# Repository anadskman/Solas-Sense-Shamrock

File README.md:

# Solas-Sense-Shamrock

A LED Lamp shaped like a shamrock that changes led color based off the room brightness.
I Named it Solas Sense so I can make different designs and Keep it simply orginized.

### My Experience
This was an easier project than most but its still fun and unquie. 
I struggled on the Designing as its an odd shape compared to just squares and a circle or two.

### Parts
- 1x Esp32-C3 SuperMini
- 3x RGB Leds Anode
- 1x Light Dependent Resistors
- 9x 220Omh Resistors
- 1x 10kOmh Resistor

- Top-Case.stl
- Bottom-Case.stl
- SolasSense-Code.ino

## BOM

| Item                    | Description         | Qty | Price (€) | URL                                                                 | Total (€) |
|-------------------------|---------------------|-----|-----------|----------------------------------------------------------------------|----------------|
| 0603 220Ω Chip          | 220Ω Resistor       | 9   | 2.07      | https://www.aliexpress.com/item/1005002783191633.html               | 2.07           |
| RGB LEDs (Anode)        | RGB LEDs (Anode)    | 3   | —         | — Pre owned                                                         | —              |
| Light Dependent Resistor| LDR                 | 1   | —         | — Pre owned                                                         | —              |
| 1005 10kΩ Chip          | 10kΩ Resistor       | 1   | 1.47      | https://www.aliexpress.com/item/1005003297094344.html               | 1.47           |
| ESP32-C3 SuperMini      | Dev Board           | 1   | 2.83      | https://www.aliexpress.com/item/1005009495310442.html               | 2.83           |
|                         |                     |     |           |                                                                     | Shipping: €1.99 | 
|                         |                      |    |            |                                                                    |Total: €8.36     |

 Schematic            |  PCB         |   Case
:-------------------------:|:-------------------------:|:-------------------------:|
 |  |

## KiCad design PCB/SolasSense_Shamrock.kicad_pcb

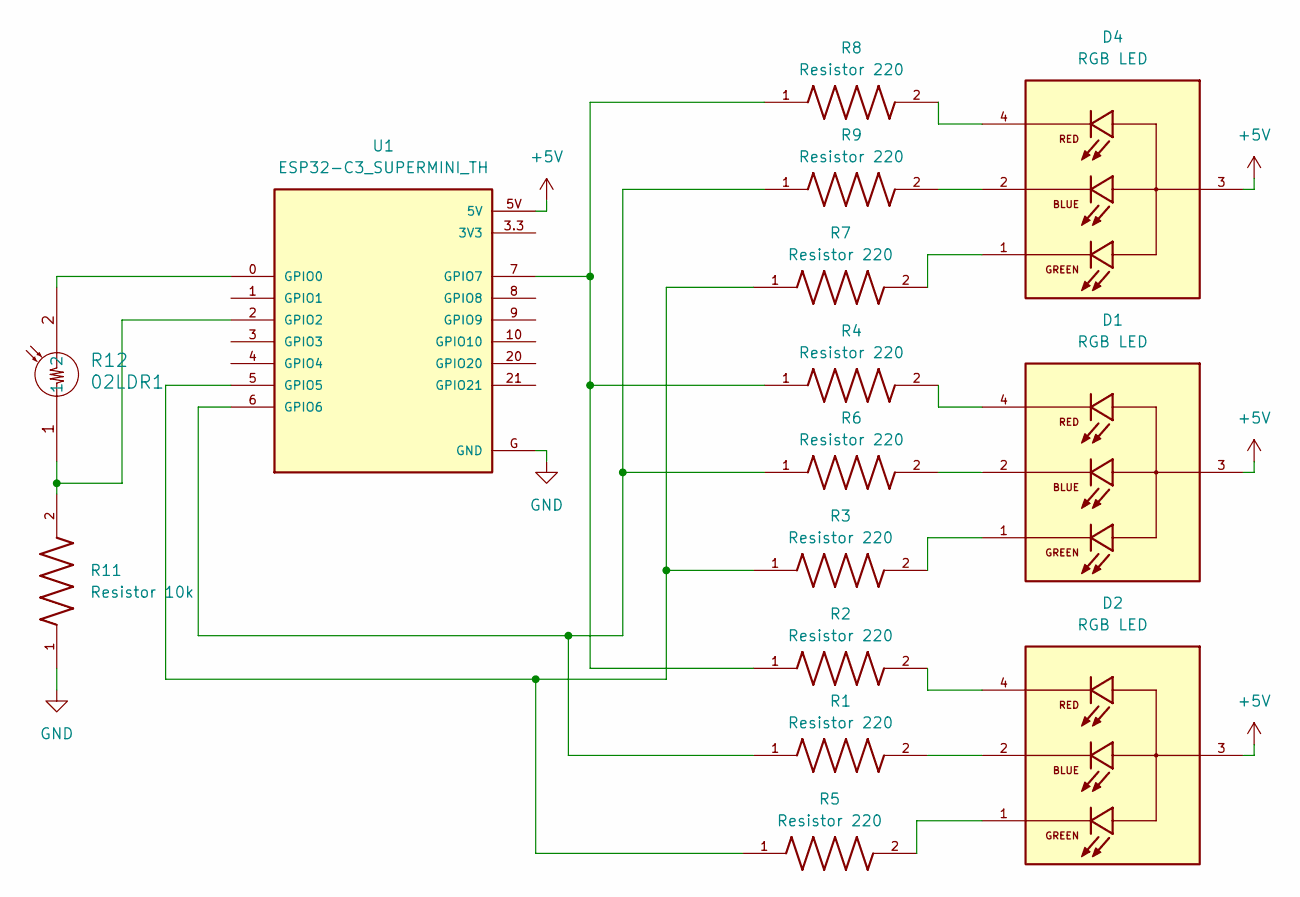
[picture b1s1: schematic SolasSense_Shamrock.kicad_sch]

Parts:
D1, D2, D4: RGB LED; LED_QBL8RGB60D0-2897; PARTREV 1.0
R1, R2, R3, R4, R5, R6, R7, R8, R9: Resistor 220; R_Axial_DIN0204_L3.6mm_D1.6mm_P5.08mm_Vertical
R11: Resistor 10k; R_Axial_DIN0204_L3.6mm_D1.6mm_P5.08mm_Vertical
R12: 02LDR1; LDR1_NTE
U1: ESP32-C3_SUPERMINI_TH; MODULE_ESP32-C3_SUPERMINI_TH

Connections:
+5V: D1.3, D2.3, D4.3, U1.5V
GND: R11.1, U1.G (GND)
unnamed: D1.1, R3.2
unnamed: D1.2, R6.2
unnamed: D1.4, R4.2
unnamed: D2.1, R5.2
unnamed: D2.2, R1.2
unnamed: D2.4, R2.2
unnamed: D4.1, R7.2
unnamed: D4.2, R9.2
unnamed: D4.4, R8.2
unnamed: R12.2, U1.0 (GPIO0)
unnamed: R11.2, R12.1, U1.2 (GPIO2)
unnamed: R3.1, R5.1, R7.1, U1.5 (GPIO5)
unnamed: R1.1, R6.1, R9.1, U1.6 (GPIO6)
unnamed: R2.1, R4.1, R8.1, U1.7 (GPIO7)

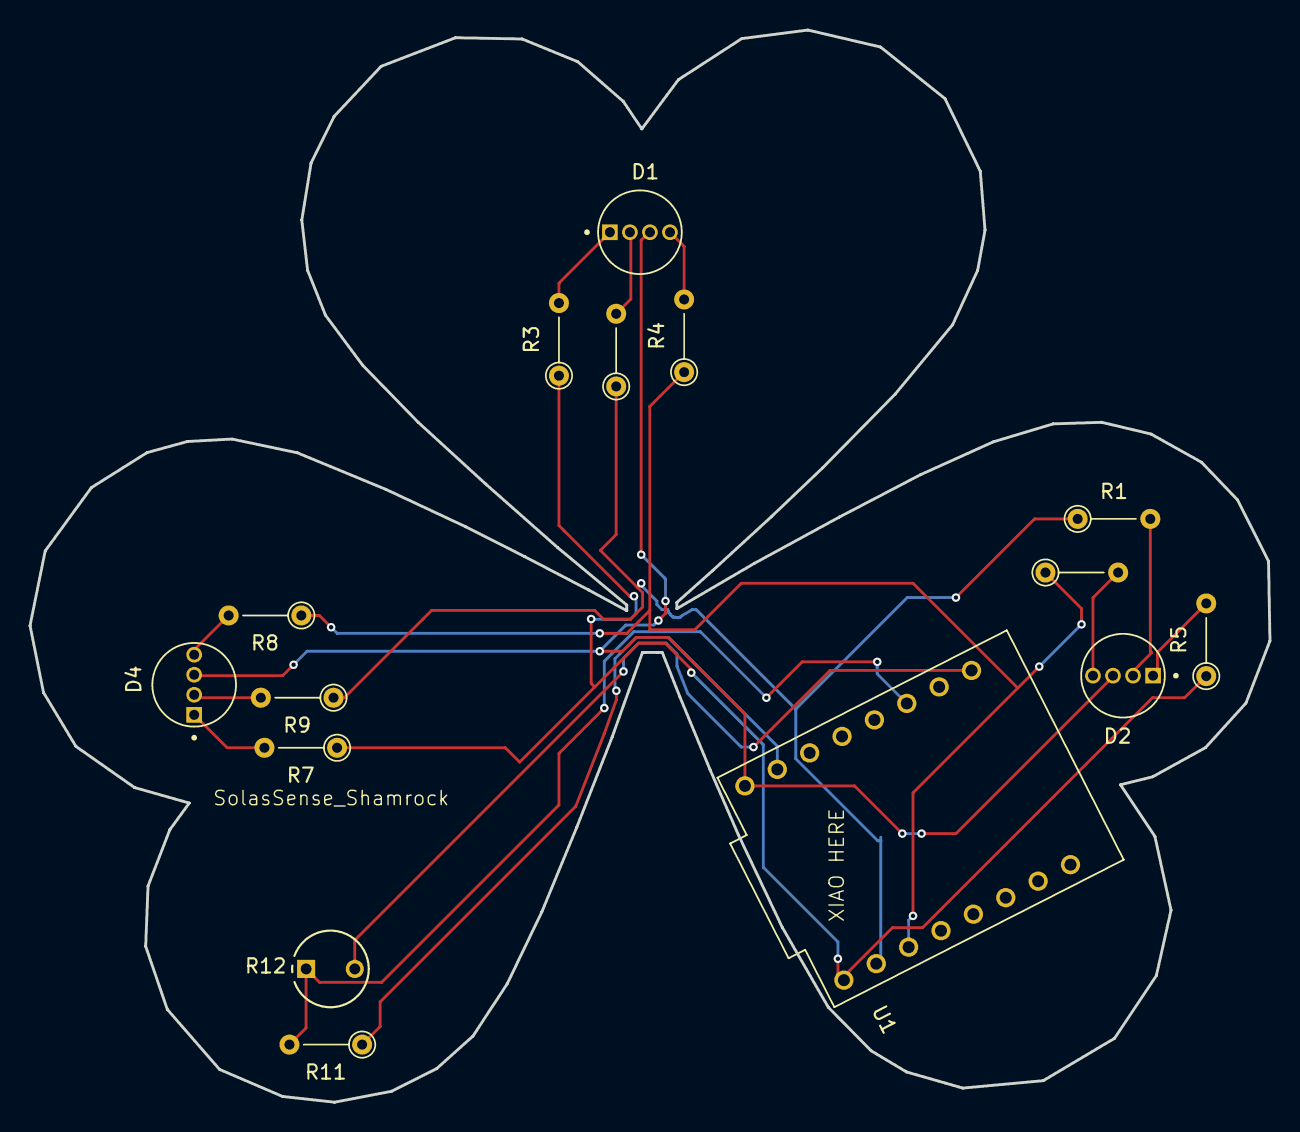
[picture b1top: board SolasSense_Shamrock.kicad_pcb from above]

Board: 2 copper layers, 86.7 x 75.0 mm, 15 parts (0 on the bottom side), 16 nets.
